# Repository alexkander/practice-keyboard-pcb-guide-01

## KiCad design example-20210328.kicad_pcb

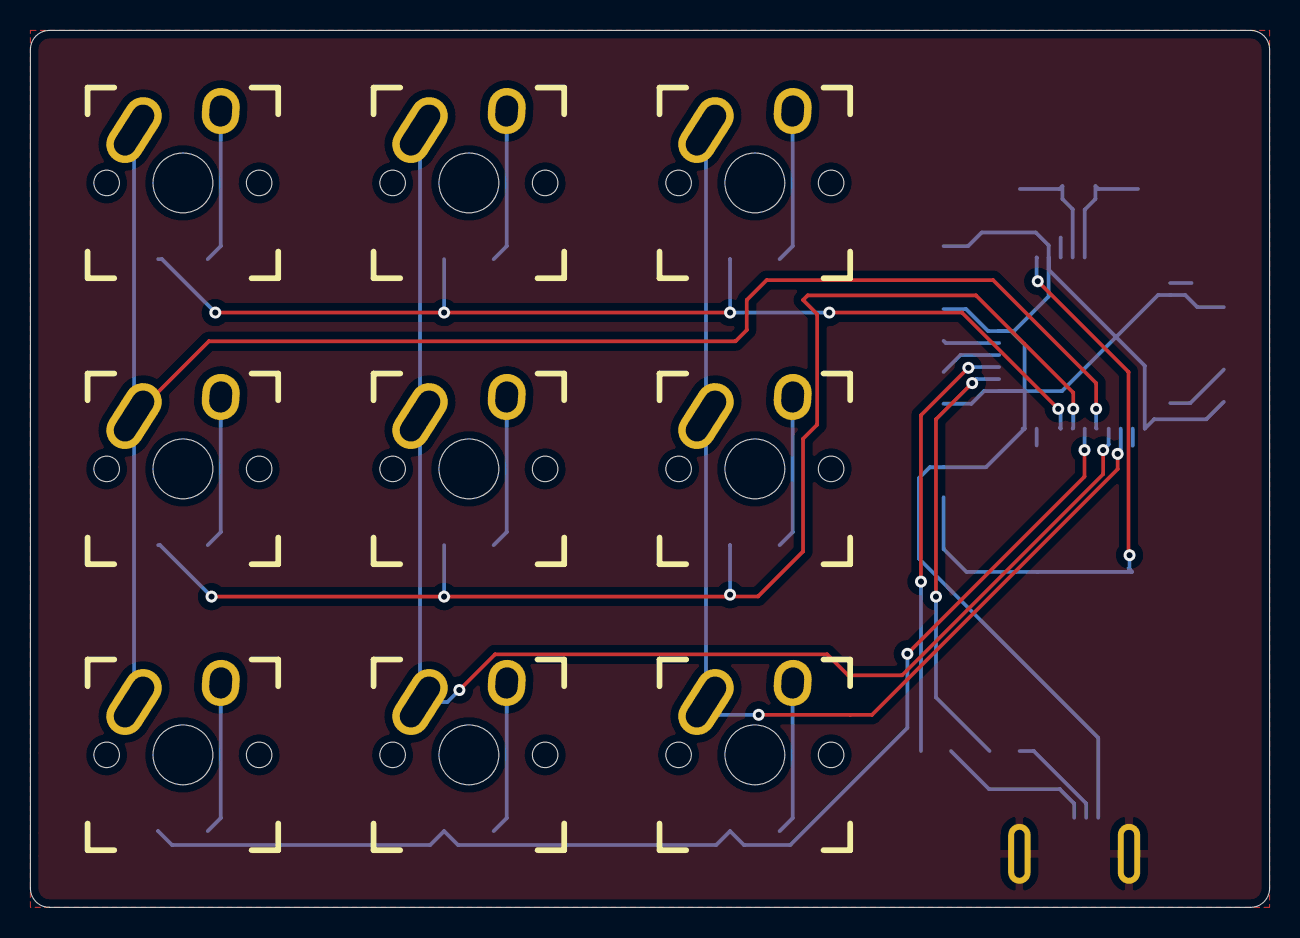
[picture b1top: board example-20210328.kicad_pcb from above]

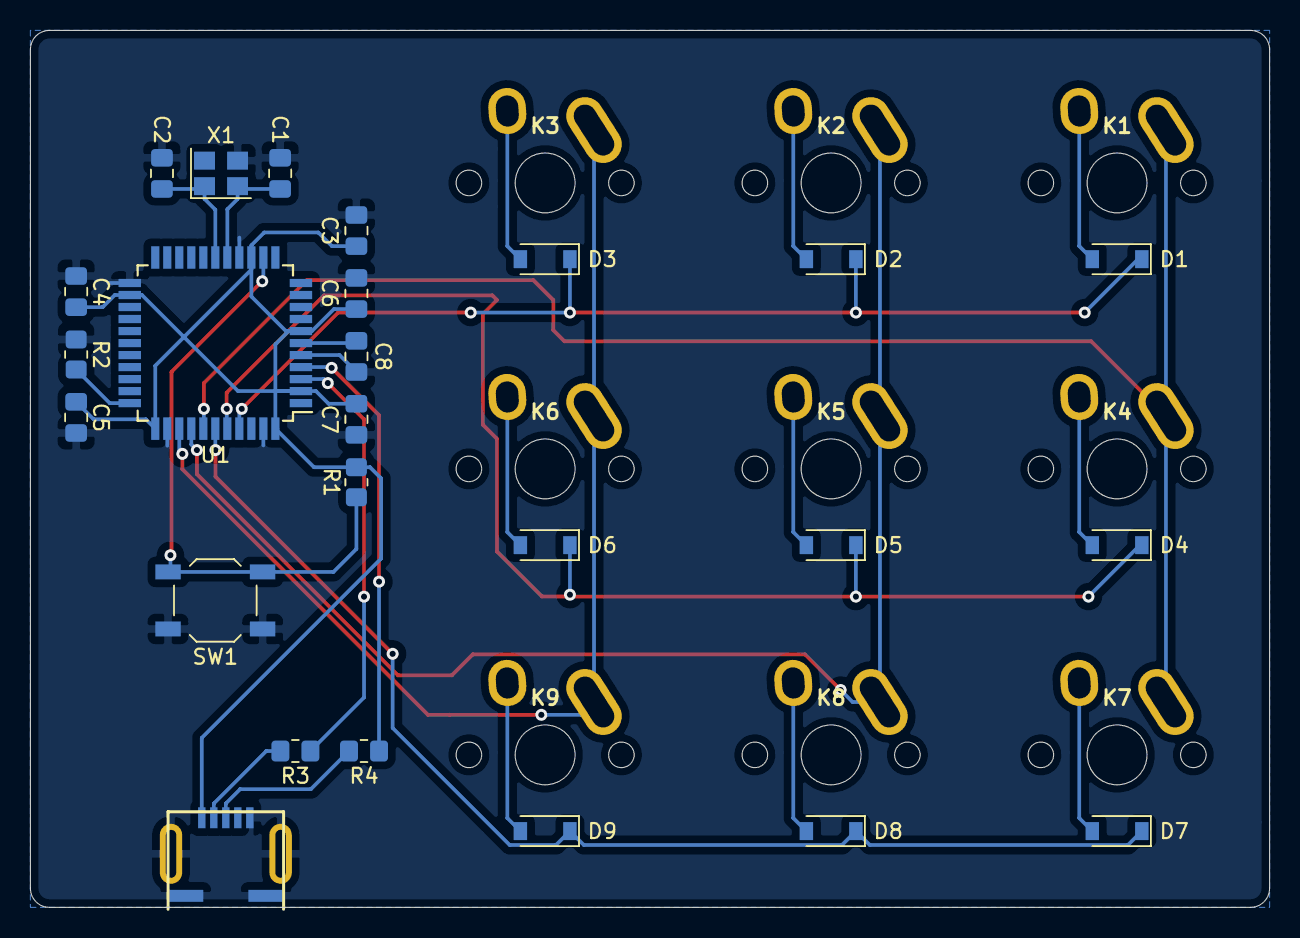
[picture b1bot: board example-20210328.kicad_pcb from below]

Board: 2 copper layers, 82.6 x 58.4 mm, 34 parts (25 on the bottom side), 26 nets.

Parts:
C1, C2: 22p; C_0805_2012Metric_Pad1.18x1.45mm_HandSolder
C3, C4, C5, C6: 0.1u; C_0805_2012Metric_Pad1.18x1.45mm_HandSolder
C7: 4.7u; C_0805_2012Metric_Pad1.18x1.45mm_HandSolder
C8: 1u; C_0805_2012Metric_Pad1.18x1.45mm_HandSolder
D1, D2, D3, D4, D5, D6, D7, D8, D9: D; D_SOD-123
J1: USB_mini_micro_B; USB_miniB_hirose_5S8
K1, K2, K3, K4, K5, K6, K7, K8, K9: KEYSW; Mx_Alps_100
R1, R2: 10k; R_0805_2012Metric_Pad1.20x1.40mm_HandSolder
R3, R4: 22; R_0805_2012Metric_Pad1.20x1.40mm_HandSolder
SW1: RESET_PUSH; SW_SPST_TL3342
U1: ATMEGA32U4; TQFP-44_10x10mm_P0.8mm
X1: XTAL_GND; Crystal_SMD_3225-4Pin_3.2x2.5mm

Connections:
/col0: K1.1, K4.1, K7.1, U1.38
/col1: K2.1, K5.1, K8.1, U1.37
/col2: K3.1, K6.1, K9.1, U1.36
/row0: D1.1, D2.1, D3.1, U1.41
/row1: D4.1, D5.1, D6.1, U1.40
/row2: D7.1, D8.1, D9.1, U1.39
GND: C1.2, C2.2, C3.2, C4.1, C5.1, C6.1, C7.2, C8.2, J1.5, J1.6, R2.1, SW1.1, U1.5, U1.15, U1.23, U1.35, U1.43, X1.3
unnamed: C1.1, U1.16, X1.2
unnamed: C2.1, U1.17, X1.1
unnamed: C8.1, U1.6
unnamed: D1.2, K1.2
unnamed: D2.2, K2.2
unnamed: D3.2, K3.2
unnamed: D4.2, K4.2
unnamed: D5.2, K5.2
unnamed: D6.2, K6.2
unnamed: D7.2, K7.2
unnamed: D8.2, K8.2
unnamed: D9.2, K9.2
unnamed: J1.2, R3.2
unnamed: J1.3, R4.2
unnamed: R1.1, SW1.2, U1.13
unnamed: R2.2, U1.33
unnamed: R3.1, U1.3
unnamed: R4.1, U1.4
VCC: C3.1, C4.2, C5.2, C6.2, C7.1, J1.1, R1.2, U1.2, U1.7, U1.14, U1.24, U1.34, U1.44

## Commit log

2021-06-13 chore: initial commit
